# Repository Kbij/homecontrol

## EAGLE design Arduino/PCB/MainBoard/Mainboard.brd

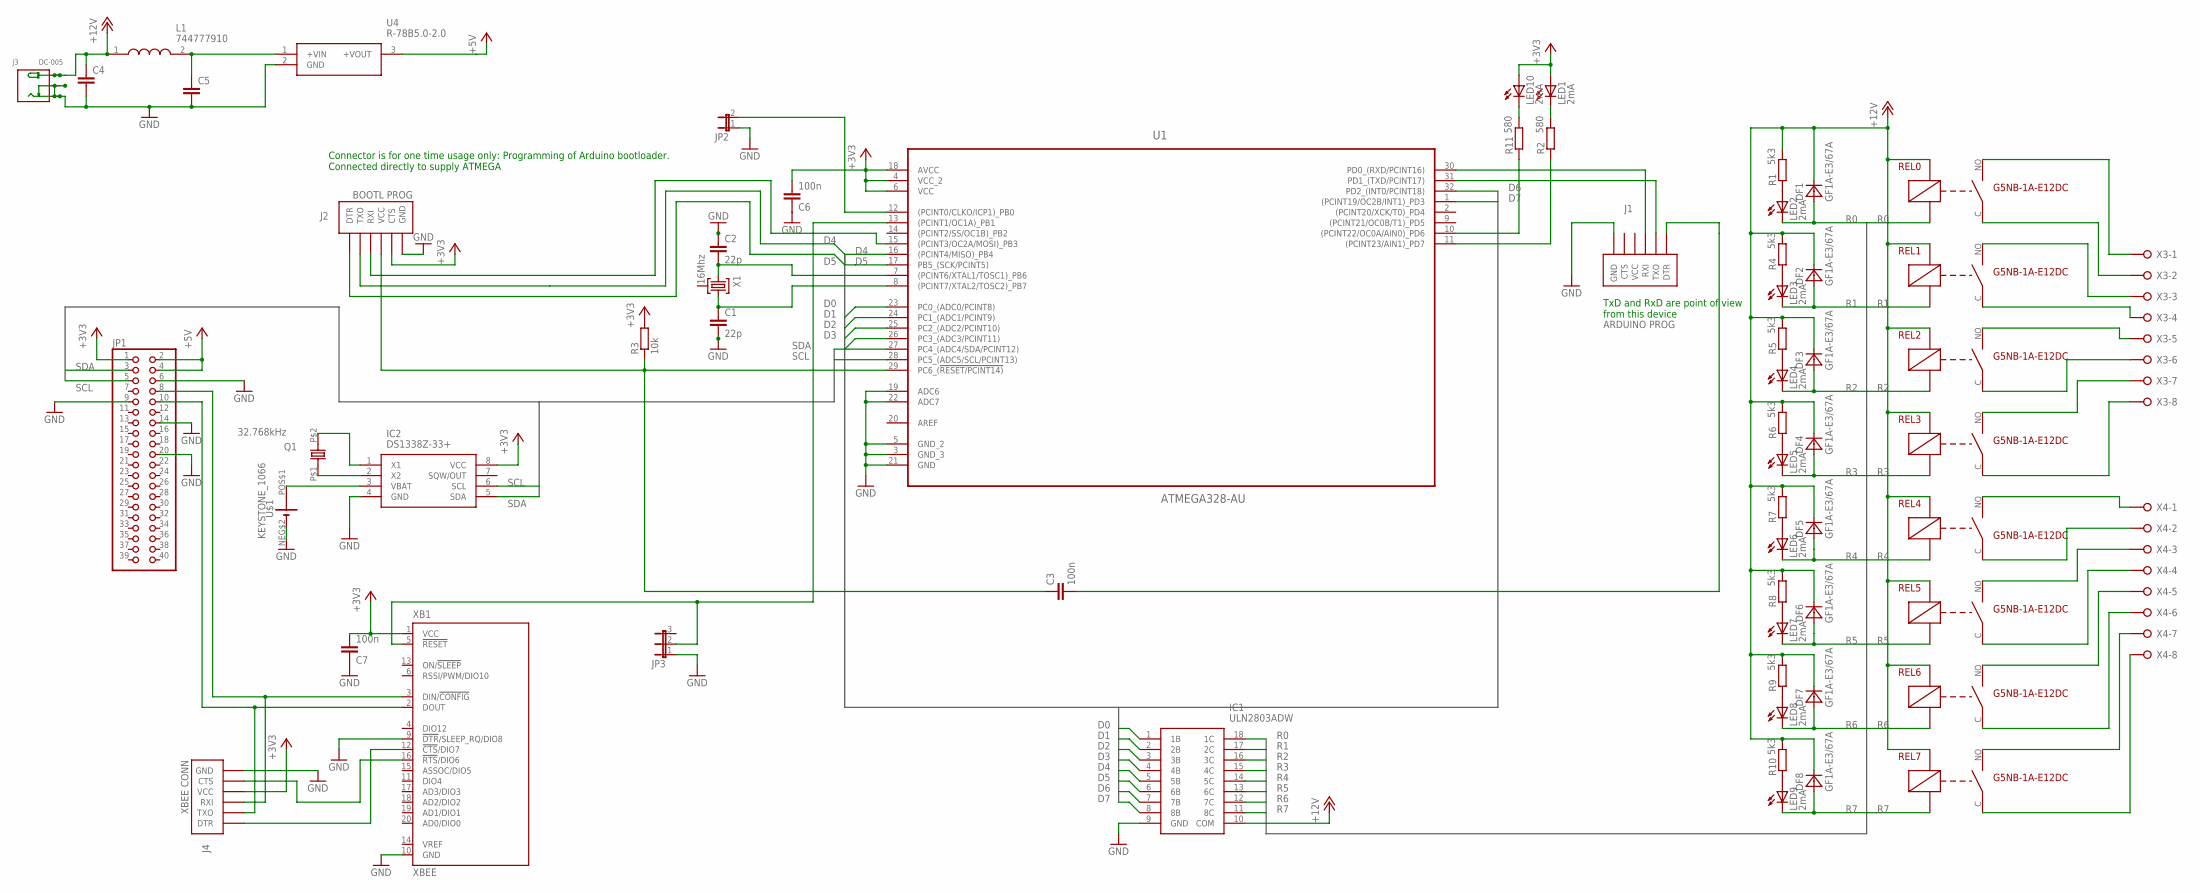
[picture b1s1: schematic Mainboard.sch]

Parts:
C1, C2: 22p; C0805
C3, C6, C7: 100n; C0805
C4, C5: C-EUC1206; C1206
DF1, DF2, DF3, DF4, DF5, DF6, DF7, DF8: GF1A-E3/67A; DO-214BA
IC1: ULN2803ADW; SOIC127P1030X265-18N
IC2: DS1338Z-33+; SOIC127P600X175-8N
J1: ARDUINO PROG; FTDI_DEVICE_SIDE
J2: BOOTL PROG; FTDI_DEVICE_SIDE
J3: DC-005; DCJ3P-14.2X11.0X9.0MM
J4: XBEE CONN; FTDI_DEVICE_SIDE
JP1: PINHD-2X20; 2X20
JP2: JUMPER_JP1E; JUMPER_JP1
JP3: JP2E; JP2
L1: 744777910; WE-PD_7332/7345_PLASTIC_BASE54
LED1, LED2, LED3, LED4, LED5, LED6, LED7, LED8, LED9, LED10: 2mA; LED3MM
Q1: 32.768kHz; CRYSAL_RADIA_6.2MM
R1, R4, R5, R6, R7, R8, R9, R10: 5k3; R0603
R2, R11: 580; R0603
R3: 10k; R0805
REL0, REL1, REL2, REL3, REL4, REL5, REL6, REL7: G5NB-1A-E12DC; G5NB-1A
U1: ATMEGA328-AU; QFP80P900X900X120-32N
U4: R-78B5.0-2.0; R-78B5
U$1: KEYSTONE_1066; KEYSTONE1066
X1: 16Mhz; HC49-3L; MPN LFXTAL003240
X3, X4: W237-08P; W237-8P
XB1: XBEE

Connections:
+3V3: C6.2, C7.2, IC2.8 (VCC), J2.P$5 (CTS), J4.P$4 (VCC), JP1.1, LED1.A, LED10.A, R3.2, U1.4 (VCC_2), U1.6 (VCC), U1.18 (AVCC), XB1.1 (VCC)
+5V: JP1.2, JP1.4, U4.3 (+VOUT)
+12V: C4.1, DF1.C, DF2.C, DF3.C, DF4.C, DF5.C, DF6.C, DF7.C, DF8.C, IC1.10 (COM), J3.+, L1.1, R1.2, R4.2, R5.2, R6.2, R7.2, R8.2, R9.2, R10.2, REL0.A1, REL1.A1, REL2.A1, REL3.A1, REL4.A1, REL5.A1, REL6.A1, REL7.A1
D0: IC1.1 (1B), U1.23 (PC0_(ADC0/PCINT8))
D1: IC1.2 (2B), U1.24 (PC1_(ADC1/PCINT9))
D2: IC1.3 (3B), U1.25 (PC2_(ADC2/PCINT10))
D3: IC1.4 (4B), U1.26 (PC3_(ADC3/PCINT11))
D4: IC1.5 (5B), J2.P$2 (TXO), U1.16 ((PCINT4/MISO)_PB4)
D5: IC1.6 (6B), J2.P$1 (DTR), U1.17 (PB5_(SCK/PCINT5))
D6: IC1.7 (7B), U1.32 (PD2_(INT0/PCINT18))
D7: IC1.8 (8B), U1.1 ((PCINT19/OC2B/INT1)_PD3)
GND: C1.2, C2.1, C4.2, C5.2, C6.1, C7.1, IC1.9 (GND), IC2.4 (GND), J1.P$6 (GND), J2.P$6 (GND), J3.-1 (-), J4.P$6 (GND), JP1.6, JP1.9, JP1.14, JP1.20, JP2.1, JP3.1, U1.3 (GND_3), U1.5 (GND_2), U1.19 (ADC6), U1.21 (GND), U1.22 (ADC7), U4.2 (GND), U$1.NEG$2 (-), XB1.9 (!DTR!/SLEEP_RQ/DIO8), XB1.10 (GND)
unnamed: C2.2, U1.7 ((PCINT6/XTAL1/TOSC1)_PB6), X1.1
unnamed: JP3.2, U1.13 ((PCINT1/OC1A)_PB1), XB1.5 (!RESET)
unnamed: J4.P$2 (TXO), JP1.10, XB1.2 (DOUT)
unnamed: REL0.NO, X3.1
unnamed: C3.2, J1.P$1 (DTR)
unnamed: C1.1, U1.8 ((PCINT7/XTAL2/TOSC2)_PB7), X1.3
unnamed: C5.1, L1.2, U4.1 (+VIN)
unnamed: R2.1, U1.11 ((PCINT23/AIN1)_PD7)
unnamed: J1.P$3 (RXI), U1.30 (PD0_(RXD/PCINT16))
unnamed: J1.P$2 (TXO), U1.31 (PD1_(TXD/PCINT17))
unnamed: LED1.K (C), R2.2
unnamed: IC2.3 (VBAT), U$1.POS$1 (+)
unnamed: J4.P$1 (DTR), XB1.12 (!CTS!/DIO7)
unnamed: IC2.2 (X2), Q1.P$1 (1)
unnamed: REL0.C, X3.2
unnamed: REL1.NO, X3.3
unnamed: REL1.C, X3.4
unnamed: REL2.NO, X3.5
unnamed: REL2.C, X3.6
unnamed: C3.1, J2.P$4 (VCC), R3.1, U1.29 (PC6_(!RESET/PCINT14))
unnamed: REL3.NO, X3.7
unnamed: J2.P$3 (RXI), U1.15 ((PCINT3/OC2A/MOSI)_PB3)
unnamed: REL7.NO, X4.7
unnamed: LED10.K (C), R11.2
unnamed: REL3.C, X3.8
unnamed: REL4.NO, X4.1
unnamed: REL4.C, X4.2
unnamed: REL5.NO, X4.3
unnamed: REL5.C, X4.4
unnamed: REL6.NO, X4.5
unnamed: REL6.C, X4.6
unnamed: REL7.C, X4.8
unnamed: JP2.2, U1.12 ((PCINT0/CLKO/ICP1)_PB0)
unnamed: J4.P$3 (RXI), JP1.8, XB1.3 (DIN/!CONFIG)
unnamed: LED2.A, R1.1
unnamed: LED3.A, R4.1
unnamed: LED4.A, R5.1
unnamed: LED5.A, R6.1
unnamed: LED7.A, R8.1
unnamed: IC2.1 (X1), Q1.P$2 (2)
unnamed: J4.P$5 (CTS), XB1.16 (!RTS!/DIO6)
unnamed: LED6.A, R7.1
unnamed: R11.1, U1.10 ((PCINT22/OC0A/AIN0)_PD6)
unnamed: LED8.A, R9.1
unnamed: LED9.A, R10.1
R0: DF1.A, IC1.18 (1C), LED2.K (C), REL0.A2
R1: DF2.A, IC1.17 (2C), LED3.K (C), REL1.A2
R2: DF3.A, IC1.16 (3C), LED4.K (C), REL2.A2
R3: DF4.A, IC1.15 (4C), LED5.K (C), REL3.A2
R4: DF5.A, IC1.14 (5C), LED6.K (C), REL4.A2
R5: DF6.A, IC1.13 (6C), LED7.K (C), REL5.A2
R6: DF7.A, IC1.12 (7C), LED8.K (C), REL6.A2
R7: DF8.A, IC1.11 (8C), LED9.K (C), REL7.A2
SCL: IC2.6 (SCL), JP1.5, U1.28 (PC5_(ADC5/SCL/PCINT13))
SDA: IC2.5 (SDA), JP1.3, U1.27 (PC4_(ADC4/SDA/PCINT12))

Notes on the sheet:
Connector is for one time usage only: Programming of Arduino bootloader. Connected directly to supply ATMEGA
TxD and RxD are point of view from this device

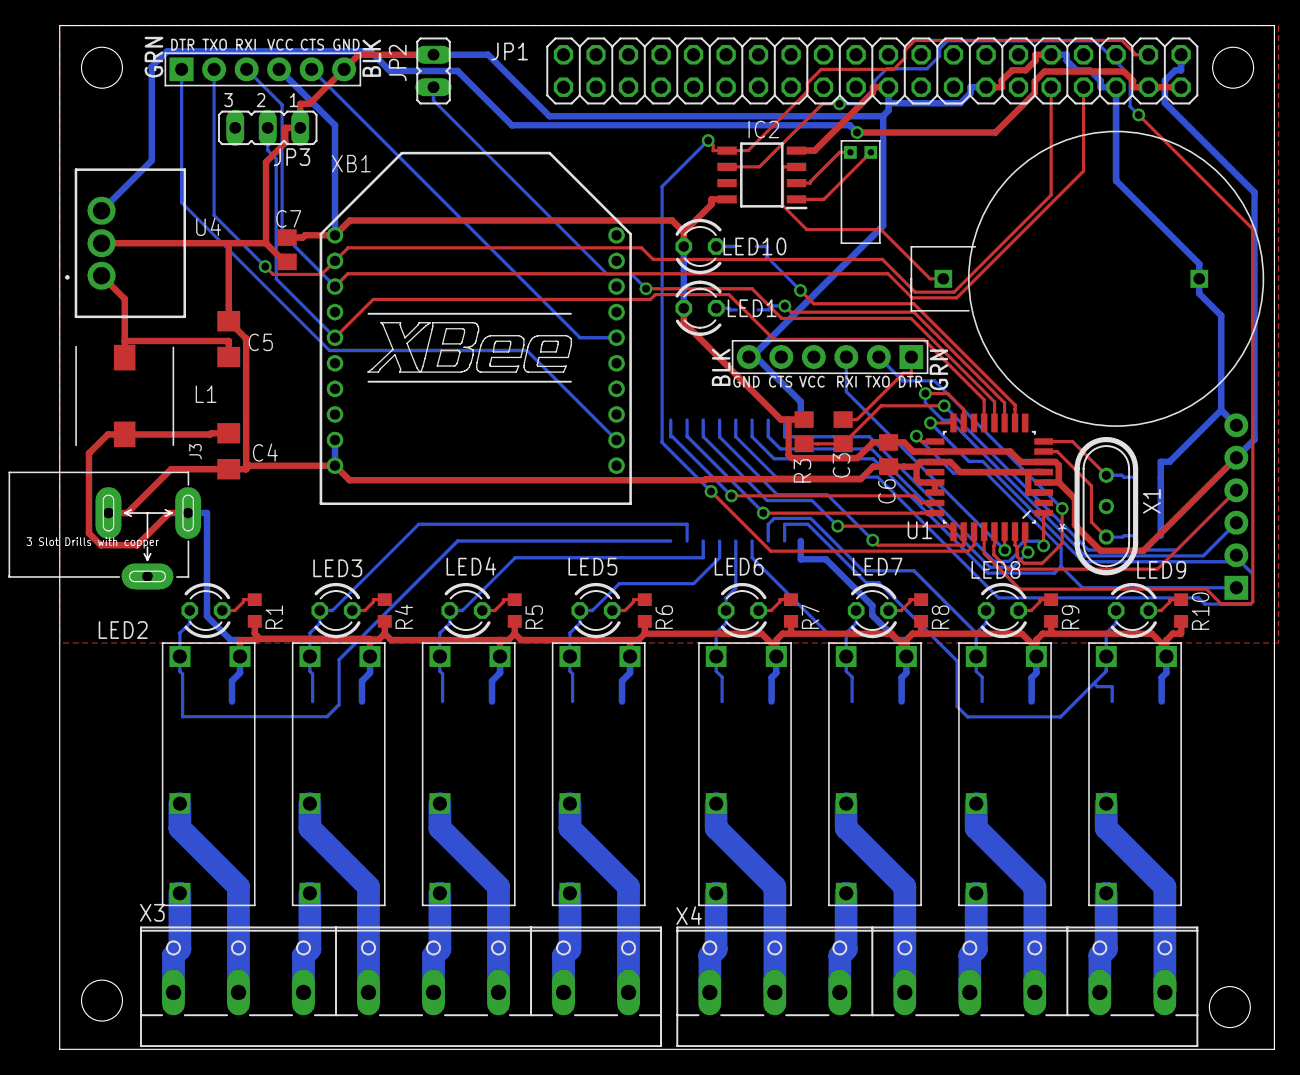
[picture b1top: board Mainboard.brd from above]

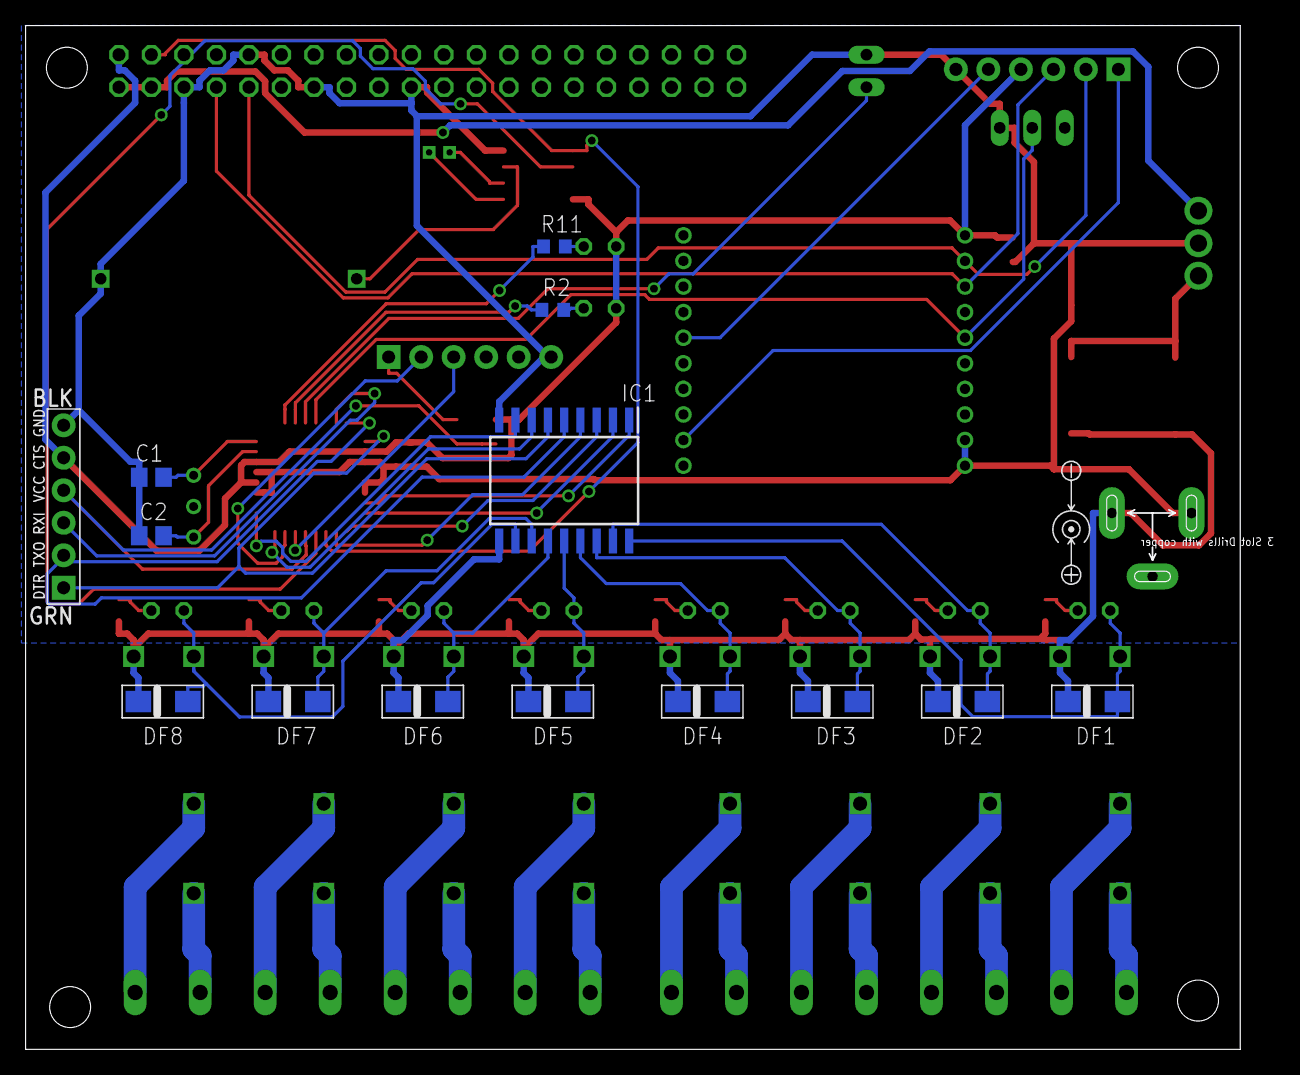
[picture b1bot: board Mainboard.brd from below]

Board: 2 copper layers, 94.9 x 80.0 mm, 62 parts (14 on the bottom side), 67 nets.

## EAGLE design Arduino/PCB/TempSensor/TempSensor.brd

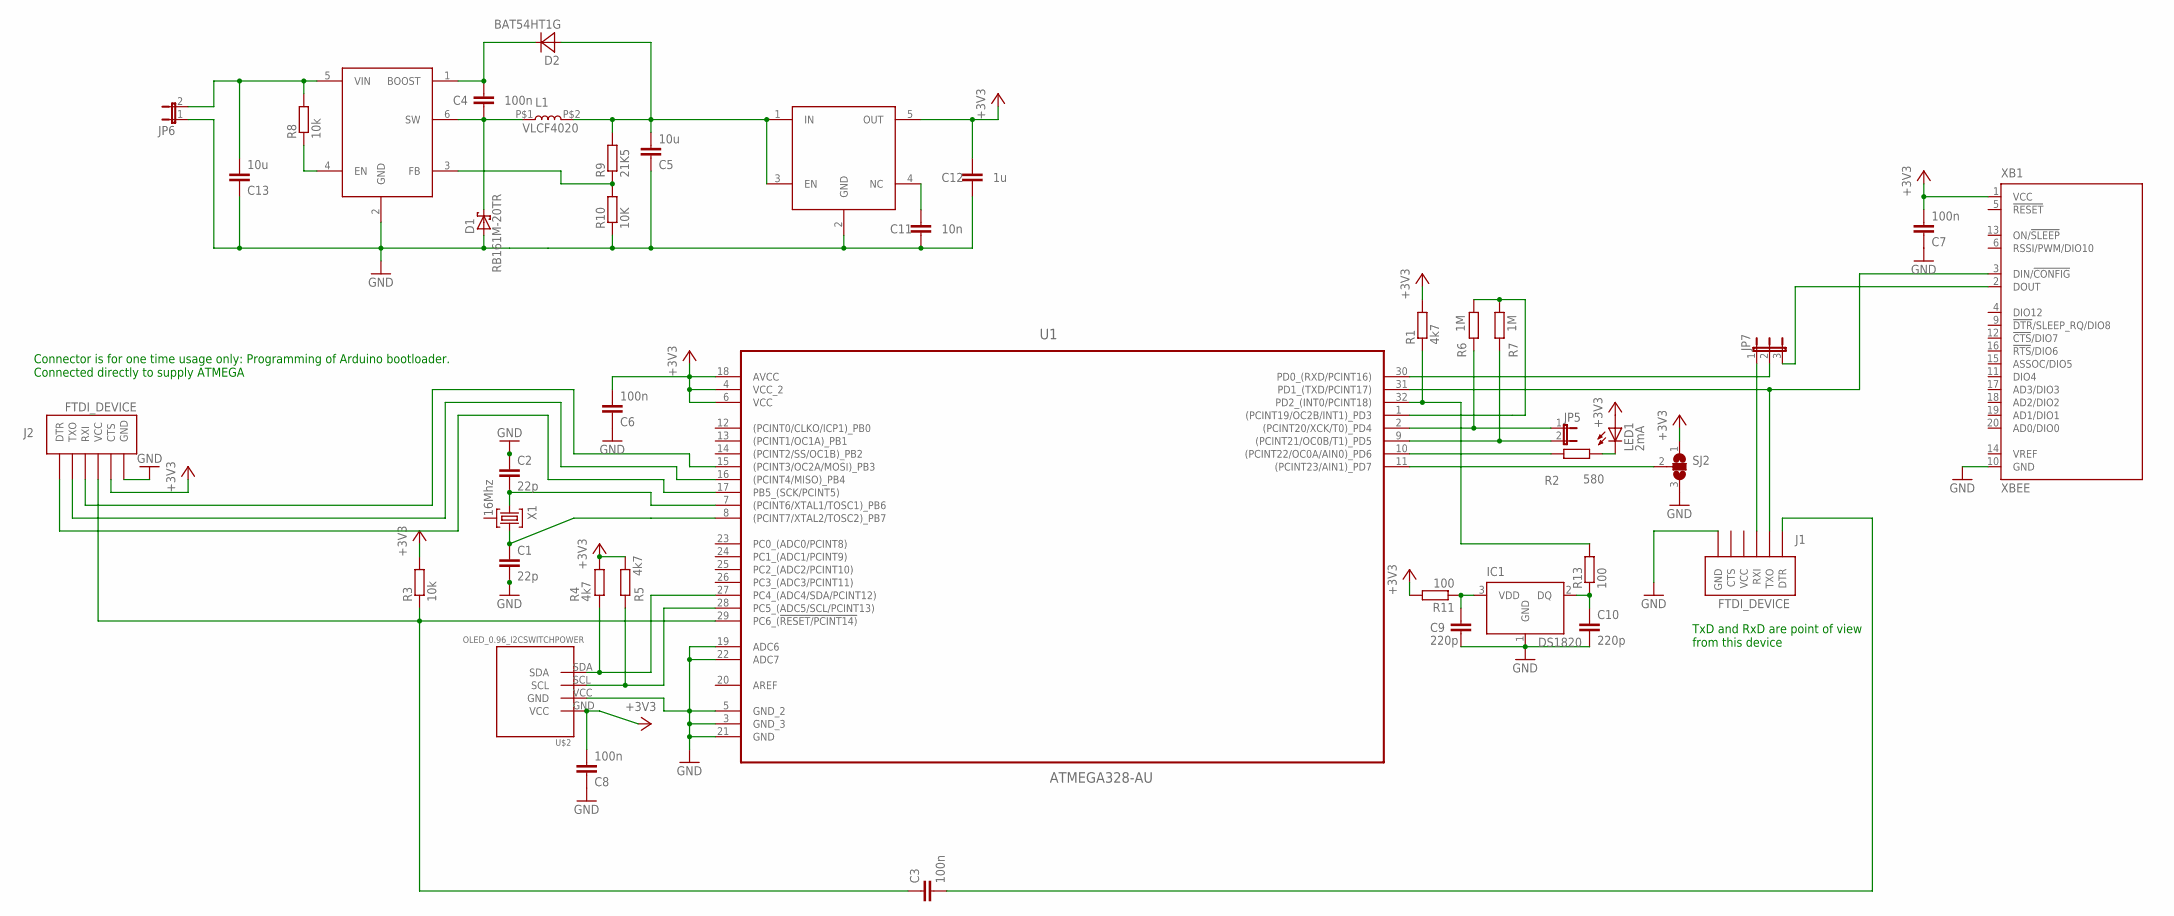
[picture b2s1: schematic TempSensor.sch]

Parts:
C1, C2: 22p; C0805
C3, C4, C6, C7, C8: 100n; C0805
C5, C13: 10u; C0805
C9, C10: 220p; C0805
C11: 10n; C0805
C12: 1u; C0805
D1: RB161M-20TR; SOD123
D2: BAT54HT1G; SOD323_ST
IC1: DS1820; TO-92
J1, J2: FTDI_DEVICE; FTDI_DEVICE_SIDE
JP5, JP6: JP1E; JP1
JP7: JP2E; JP2
L1: VLCF4020
LED1: 2mA; LED3MM
R1, R4, R5: 4k7; R0805
R2: 580; R0603
R3, R8: 10k; R0805
R6, R7: 1M; R0805
R9: 21K5; R0805
R10: 10K; R0805
R11, R13: 100; R0805
SJ2: SJ2W; SJ_2
U1: ATMEGA328-AU; QFP80P900X900X120-32N
U2: LM2736X; SOT23-6L
U3: XC6210; SOT23-5
U$2: OLED_0.96_I2CSWITCHPOWER; OLED_0.96_I2C
X1: 16Mhz; HC49-3L; MPN LFXTAL003240
XB1: XBEE

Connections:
+3V3: C6.2, C7.2, C8.2, C12.2, J2.P$5 (CTS), LED1.A, R1.2, R3.2, R4.2, R5.2, R11.2, SJ2.1, U1.4 (VCC_2), U1.6 (VCC), U1.18 (AVCC), U3.5 (OUT), U$2.GND (VCC), XB1.1 (VCC)
GND: C1.2, C2.1, C5.1, C6.1, C7.1, C8.1, C9.1, C10.1, C11.1, C12.1, C13.1, D1.A, IC1.1 (GND), J1.P$6 (GND), J2.P$6 (GND), JP6.1, R10.1, SJ2.3, U1.3 (GND_3), U1.5 (GND_2), U1.19 (ADC6), U1.21 (GND), U1.22 (ADC7), U2.2 (GND), U3.2 (GND), U$2.VCC (GND), XB1.10 (GND)
unnamed: C2.2, U1.7 ((PCINT6/XTAL1/TOSC1)_PB6), X1.1
unnamed: C1.1, U1.8 ((PCINT7/XTAL2/TOSC2)_PB7), X1.3
unnamed: J1.P$3 (RXI), JP7.1
unnamed: JP7.2, U1.30 (PD0_(RXD/PCINT16))
unnamed: J1.P$2 (TXO), U1.31 (PD1_(TXD/PCINT17)), XB1.3 (DIN/!CONFIG)
unnamed: R1.1, R13.2, U1.32 (PD2_(INT0/PCINT18))
unnamed: R6.2, R7.2, U1.1 ((PCINT19/OC2B/INT1)_PD3)
unnamed: C4.1, D1.C, L1.P$1 (1), U2.6 (SW)
unnamed: JP5.1, R6.1, U1.2 ((PCINT20/XCK/T0)_PD4)
unnamed: JP5.2, R7.1, U1.9 ((PCINT21/OC0B/T1)_PD5)
unnamed: R9.1, R10.2, U2.3 (FB)
unnamed: LED1.K (C), R2.2
unnamed: R2.1, U1.10 ((PCINT22/OC0A/AIN0)_PD6)
unnamed: SJ2.2, U1.11 ((PCINT23/AIN1)_PD7)
unnamed: JP7.3, XB1.2 (DOUT)
unnamed: C4.2, D2.C, U2.1 (BOOST)
unnamed: C3.1, J2.P$4 (VCC), R3.1, U1.29 (PC6_(!RESET/PCINT14))
unnamed: C3.2, J1.P$1 (DTR)
unnamed: J2.P$3 (RXI), U1.15 ((PCINT3/OC2A/MOSI)_PB3)
unnamed: J2.P$1 (DTR), U1.17 (PB5_(SCK/PCINT5))
unnamed: J2.P$2 (TXO), U1.16 ((PCINT4/MISO)_PB4)
unnamed: R8.1, U2.4 (EN)
unnamed: C9.2, IC1.3 (VDD), R11.1
unnamed: C10.2, IC1.2 (DQ), R13.1
unnamed: C11.2, U3.4 (NC)
SCL: R5.1, U1.28 (PC5_(ADC5/SCL/PCINT13)), U$2.SCL
SDA: R4.1, U1.27 (PC4_(ADC4/SDA/PCINT12)), U$2.SDA
VIN: C13.2, JP6.2, R8.2, U2.5 (VIN)
VO: C5.2, D2.A, L1.P$2 (2), R9.2, U3.1 (IN), U3.3 (EN)

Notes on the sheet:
Connector is for one time usage only: Programming of Arduino bootloader. Connected directly to supply ATMEGA
TxD and RxD are point of view from this device

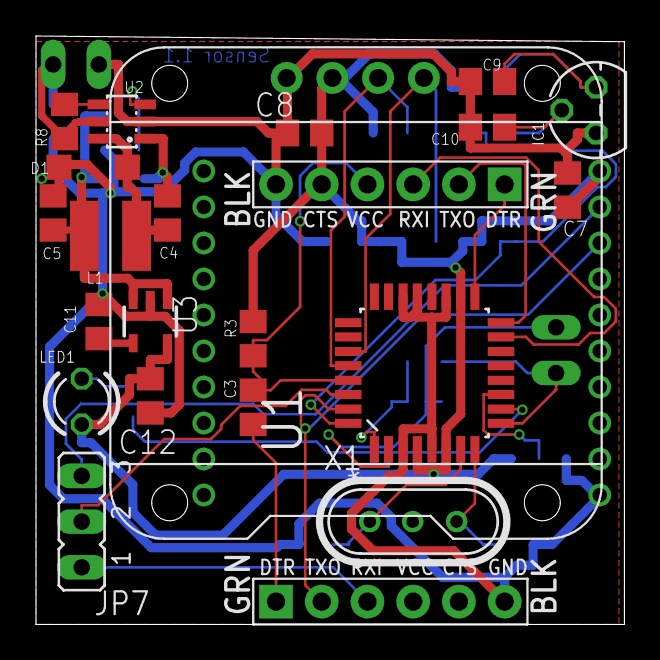
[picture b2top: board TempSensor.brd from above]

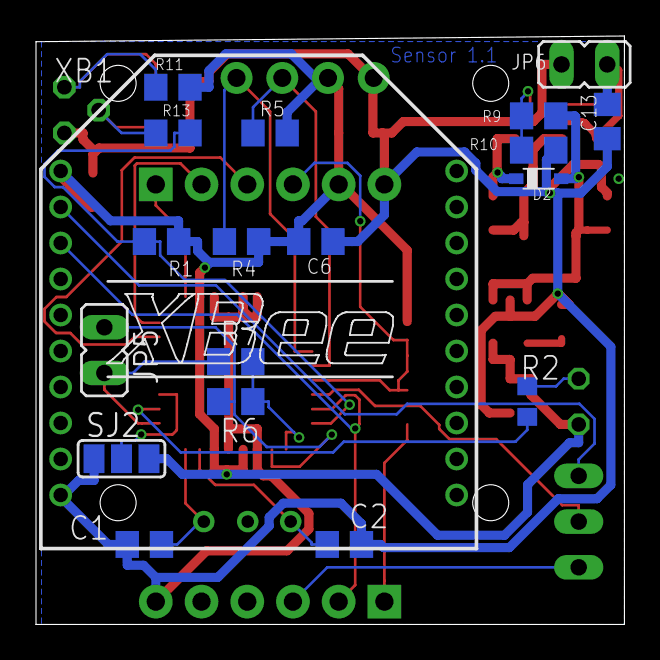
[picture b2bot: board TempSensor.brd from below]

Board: 2 copper layers, 32.7 x 32.7 mm, 42 parts (19 on the bottom side), 31 nets.

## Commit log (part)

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2016-03-20 Base project
2016-03-20 Comm and service added
2016-03-23 homecontrol
2016-03-28 Home control server
2016-03-28 libraries
2016-03-28 test working
2016-03-29 bugfix commmodel
2016-03-29 test server and loghost
2016-03-30 comm
2016-03-31 clientsocket working
2016-04-04 server
2016-04-05 live tests
2016-04-06 json parsing
2016-04-06 test
2016-04-06 move commobjects
2016-04-06 move comm objects
2016-04-06 client timeouts
2016-04-07 working
2016-04-08 with writer
2016-04-10 try catch
2016-04-12 cleanup
2016-04-23 CommModel Maintenance thread, Cloudsocket
2016-05-17 monitor changes
2016-05-17 socket and various other, still not working
2016-05-17 small changes
2016-05-17 sql create tables
2016-05-17 more logging
2016-05-17 chang log levels
2016-05-23 Better. But still not working
2016-05-28 arduino first commit
2016-05-30 Touch library
2016-05-30 Sending formatted output to xbee
2016-05-31 more precision
2016-05-31 write temperature to db
2016-06-01 testdata
2016-06-01 LPF filter
2016-06-01 adding filter
2016-06-01 added test
2016-06-02 moving verage filter
2016-06-02 new tables
2016-06-03 insert new sensor
2016-06-05 rename
2016-06-08 missing
2016-06-10 Simulator, sending roomtemperature to cloud
2016-06-10 Sending objects to the cloud
2016-06-12 temperature monitoring
2016-06-13 mem leaks + mysql threadinit threadend
2016-06-14 unregister clientsocket
2016-06-14 fix test & build info
2016-06-14 new test data
2016-06-16 filter
2016-06-16 rename temperaturesensorsIf to TemperatureSourceIf
2016-06-16 filter startup
2016-06-18 double in temperature filter& logging
2016-07-02 Digimesh lib
2016-07-05 changed Serial class
2016-07-06 DM serial
2016-07-06 serial port flag
2016-07-06 added boost_thread
2016-07-06 cmake
2016-07-07 Serial working
2016-07-07 frame processor + tests
2016-07-08 added frame processor
2016-07-11 Retrieve SN
2016-07-13 tx test
2016-07-13 Working Unicast Communication !!! :-)
2016-08-06 Arduino code
2016-08-18 comm enhancements
2016-08-18 xbee comm
2016-08-18 fix build
2016-10-03 fix mem leaks in tests + fix hang
2016-10-28 cleanup + software serial debug
2016-10-29 unfirtered temperature logging
2016-10-29 fix log
2016-11-06 sensor pcb
2016-11-07 log without filtering
2016-11-07 filter, round less
2016-11-11 weighted exponential filter
2016-11-13 send calibration
2016-11-13 writeCalibration
2016-11-13 temperature viewer
2016-11-13 Board as send
2016-11-13 Filter + Calibration
2016-11-22 set sensor resolution
2016-11-22 sleep
2016-11-23 fix filter
2016-11-24 As installed
2016-11-27 send roomName to sensor
2016-11-27 NI command
2016-11-27 Room name, NI command
2016-11-30 Retry = 3, no lowpower
2016-12-01 channel change
2016-12-01 change channel
2016-12-02 auto associate
2016-12-11 zigbee channel
2016-12-11 Channel 26
2016-12-11 channel 25
2016-12-12 channel 0x19
2016-12-12 channel 1A
2016-12-12 Channel 0x1A
2016-12-21 xbee channel
2017-01-04 base board
2017-01-10 Voor aanpassing board (verplaatsen toetsen en xbee)
2017-01-11 met manuele routing power
2017-01-13 xbee/oled positie + power routed
2017-01-13 power routed
2017-01-16 power routed/ labels placed
2017-01-16 input cap toegevoegd
2017-01-23 logging
2017-01-26 sensor changes
2017-01-28 as Send to allpcb
2017-01-30 Set temperature up/down
2017-03-05 component values
2017-03-12 part values
2017-03-28 name in logging
2017-06-26 download http
2017-07-12 disconnect logging (mLastFrameTime)
2017-07-12 disconnect logging
2017-07-26 fix crash
2017-07-27 homecontrol connection debugging
2017-08-21 missing includes
2017-08-22 library search path
2017-08-23 dbschema
2017-10-10 linux startup
2018-01-13 move sql
2018-02-07 Other channel + new layout oled
2018-02-07 gmap etc
2018-03-06 Mainboard
2018-03-31 db schema
2018-04-02 system clock
2018-04-02 write time to sensors
2018-04-02 broadcast 3 times
2018-04-02 don't wait for response when broadcast time
2018-04-02 recursive mutex
2018-04-02 Receive time & enable up/down buttons
2018-04-02 less logging
2018-04-14 working, not interrupt safe
2018-04-15 maiboard control (visual studio project)
2018-04-20 ready to send v2
2018-04-23 added tests
2018-05-12 lastest board version
2018-05-21 driver
2018-12-16 working again
2018-12-23 foreground service
2018-12-26 send location interval
2018-12-26 no interval for a not connected client
2018-12-26 with location interval
2018-12-26 geofence in comments
2018-12-26 log battery level
2018-12-27 behuizing
2018-12-31 met bevestiging
2019-01-08 final behuizing
2019-01-12 fix crash tcp server
2019-01-12 send battery level
2019-01-12 support for location interval and battery level
2019-01-13 full version, first version
2019-01-13 heater logging
2019-01-13 write heater state
2019-01-14 send heater on/off
2019-01-14 fix xbee comm
2019-01-14 heater feedback working
2019-01-16 default set = 21
2019-01-16 set temp
2019-01-17 set AP mode
2019-01-17 fix deadlock
2019-01-25 set api mode
2019-01-29 Tests
2019-01-29 simulator
2019-02-11 async socket + other
2019-02-13 cleanup & logging
2019-02-13 simulation
2019-02-13 shared lib
2019-02-14 new lib
2019-02-14 dxdt, dxdt2
2019-05-28 multiple years
2020-01-08 add platform.io project
2020-01-10 too large
2020-01-10 compiles, exclude capacitive sensors
2020-01-12 SendosDisplay class
2020-01-12 added FilteredTemperatureSensor
2020-01-12 incl temperature sensor (not working)
2020-08-23 location fix, android 9.0
2021-10-12 - fix reconnect
2021-10-12 - new server - filter location - filter location unit test
2021-10-21 - communication is stable (and always on)
2022-02-11 Bump Google.Protobuf in /HomeControl/WindowsMonitor
    Bumps [Google.Protobuf](https://github.com/protocolbuffers/protobuf) from 3.14.0 to 3.15.0.
    - [Release notes](https://github.com/protocolbuffers/protobuf/releases)
    - [Changelog](https://github.com/protocolbuffers/protobuf/blob/master/generate_changelog.py)
    - [Commits](https://github.com/protocolbuffers/protobuf/compare/v3.14.0...v3.15.0)
    ---
    updated-dependencies:
2022-05-19 - building sysroots
2022-05-23 - cross build working
2022-11-16 - add bootstrap file
2022-11-16 - fix
2022-11-19 - fix shared_ptr issue, added mutex
2023-04-11 -fix haning sockets
2023-05-30 Bump BouncyCastle from 1.8.5 to 1.8.9 in /HomeControl/WindowsMonitor
    Bumps BouncyCastle from 1.8.5 to 1.8.9.
    ---
    updated-dependencies:
    - dependency-name: BouncyCastle
    dependency-type: direct:production
    ...
2025-01-21 gps logger
2025-01-21 - test new login
2025-02-01 - single mysql session
2025-02-01 - fix error
2025-02-05 - Windows monitor

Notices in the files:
parts and their libraries:
SparkFun-Connectors: Licensing: Creative Commons ShareAlike 4.0 International - https://creativecommons.org/licenses/by-sa/4.0
